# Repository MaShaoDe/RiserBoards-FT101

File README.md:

# RB Riser Boards for Yaesu FT-101 and Sommerkamp FT-277 Transceivers

*Because aligning a plug-in card with your nose inside the chassis is a tradition no OM or YL needs to keep.*

**No CAD skills needed, no special tools, no excuses.** Grab the Gerber ZIP, upload it to JLCPCB, order a card edge connector, and a week later the postman brings you a pack of shiny gold fingered boards. Heat up the iron, solder 36 joints, beep them through, and your FT-101 opens up like it never did before. That is the DIY spirit that built ham radio: you build it, you understand it, you fix it. Let's go!

The Yaesu FT-101 family, sold in Europe as the Sommerkamp FT-277, earned the nickname "the workhorse" for good reason: almost every circuit sits on a plug-in card that drops into an edge connector in the chassis. Great for service. Less great when you want to measure a card while it is running, because then it is buried between its neighbours.

A riser board solves that, QSL? It plugs into the socket in the radio, and the card plugs into the riser. The card now stands about 10 cm higher, in line with its original position, and every trimmer, test point and component is within reach of your probe. Each contact also gets its own test pad on the riser, top and bottom.

## Which radios?

Every model of the original series with plug-in cards:

| Brand | Models |
|---|---|
| Yaesu | FT-101 (Mk I, Mk II), FT-101B, FT-101E, FT-101EE, FT-101EX, FT-101F, FT-101FE, FT-101FX (plus the Japanese BS and ES versions) |
| Sommerkamp | FT-277, FT-277B, FT-277E, FT-277EE |

Not for the FT-101Z and FT-101ZD. Despite the name they are a different design without plug-in cards. Sorry, Z owners, negative copy on this one.

## Which riser for which card?

The number in the name is the count of contacts per side. That is also how to pick one: count the fingers on one side of your card, or measure the width of the finger zone.

| Riser | Contacts | Finger zone | Cards | Status |
|---|---|---|---|---|
| [RB10](hardware/riser-2x10) | 2x10 | 42 mm | PB-1292 noise blanker | V0.3 in production |
| [RB14](hardware/riser-2x14) | 2x14 | 57 mm | PB-1184A modulator and oscillator | V0.3 in production |
| [RB18](hardware/riser-2x18) | 2x18 | 73 mm | PB-1180B HF IF, PB-1181B RF, PB-1314 regulator | V0.1 prototype built, V0.3 in production |
| [RB22](hardware/riser-2x22) | 2x22 | 89 mm | PB-1183B IF, PB-1315A AF | V0.3 in production |

Card names vary between production runs. If your card has the right width, it fits.

## Build one in four steps

1. **Download** the Gerber ZIP of your riser: [RB10](hardware/riser-2x10/RB10_V0.3_gerber.zip), [RB14](hardware/riser-2x14/RB14_V0.3_gerber.zip), [RB18](hardware/riser-2x18/RB18_V0.3_gerber.zip) or [RB22](hardware/riser-2x22/RB22_V0.3_gerber.zip).
2. **Order** bare boards at the PCB maker of your choice. The fabrication specification is in [docs/ordering.md](docs/ordering.md). The one thing you must not forget: **gold fingers**, 1.6 mm, ENIG.
3. **Buy** one card edge connector per board, see [docs/bom.md](docs/bom.md).
4. **Solder** the connector and start measuring, see [docs/assembly.md](docs/assembly.md).

Total cost for five RB18 boards plus connectors: roughly the price of a nice dinner for two, and a lot less than a burnt card. Share the spare boards with the OMs in your club and the whole local net is QRV for service.

## What is on the board

- FR4, 1.6 mm, 105 mm long, in-line design: the card stands straight above the socket
- Hard gold edge fingers on both sides with a bevelled tip
- 2 mm traces, top and bottom kept separate, all covered by solder mask
- One test pad per contact on both sides, in line with the card's pins
- Clear silkscreen: riser type, compatible radios, "COMPONENT SIDE" and an arrow towards the radio, so the card goes in the right way round
- No pin numbers printed. The cards in this family number their pins in different directions, so the riser would be wrong on half of them. Read the number on the card itself.

## A word about RF and IF cards

The riser makes the signal path about 10 cm longer. Supply voltages, bias and audio do not care. Tuned RF and IF circuits (PB-1180B, PB-1181B, PB-1183B) may, and you would rather not hunt self-made QRM. Use the riser there to measure voltages and levels, and do the fine alignment with the card back in its own socket.

## Contents

- [docs/specification.md](docs/specification.md): measurements, design decisions, open questions
- [docs/ordering.md](docs/ordering.md): fabrication specification for any PCB maker
- [docs/bom.md](docs/bom.md): parts to buy
- [docs/assembly.md](docs/assembly.md): soldering, checking and using the riser
- `hardware/`: one folder per riser with the Gerber ZIP and a picture of both sides
- `hardware/archive/`: Gerber files of the first RB18 prototype (V0.1)

## Licenses

- Hardware (Gerber files): CERN-OHL-P-2.0
- Documentation and pictures: CC-BY-4.0

See [LICENSE.md](LICENSE.md). You may build, sell and modify the boards. If you change the design, please give it a name of your own and do not call it RB10, RB14, RB18 or RB22, so that the tested original stays recognisable.

## Disclaimer

Use at your own risk. The FT-101 carries high voltages in the PA section, and the riser does not change that. This project has no connection to Yaesu or Sommerkamp. The names are used only to state compatibility.

## Contributing

Measurements of other cards, corrections, photos and stories of successful repairs are welcome. Open an issue or a pull request, we copy you 5 and 9.

Questions, ideas or wishes for changes? Just call in by opening an issue on GitHub. No promises on what gets built or when, this is a hobby project run in spare time between QSOs, but every message is read and the band is always open.

## Thank you

To Yaesu for building a radio that people still repair with love fifty years later, to Sommerkamp for bringing it to Europe, to everyone who keeps the service manuals and board lists online, and to every OM and YL who keeps an old workhorse on the air.

May your filaments glow and your SWR stay flat.

73 de Marcel (MaShaoDe)

Copyright 2026 FerienBSD aka Marcel Sauder (MaShaoDe)

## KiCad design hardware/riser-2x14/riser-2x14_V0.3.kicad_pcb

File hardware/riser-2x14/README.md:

# RB14: Riser 2x14 (28 contacts)

For cards: PB-1184 (modulator and oscillator)

Current version: **V0.3**, in production since 2026-11-25.

## Files

| File | Content |
|---|---|
| [`RB14_V0.3_gerber.zip`](RB14_V0.3_gerber.zip) | Gerber and drill files, ready to upload to any PCB maker |
| `RB14_V0.3.png` | Both sides, rendered from the Gerber files |

## Board

| Item | Value |
|---|---|
| Outline | 62 x 105 mm (finger zone 57 mm wide, 11 mm long) |
| Contacts | 2x14, pitch 3.96 mm, contact field 51.48 mm |
| Edge fingers | 2.0 x 9.0 mm, both sides |
| Test pads | round 2.6 mm, both sides, one per contact |
| Connector pads | 2.0 x 5.0 mm, both sides |

Fabrication settings: [../../docs/ordering.md](../../docs/ordering.md). Connector: [../../docs/bom.md](../../docs/bom.md). Soldering and use: [../../docs/assembly.md](../../docs/assembly.md).

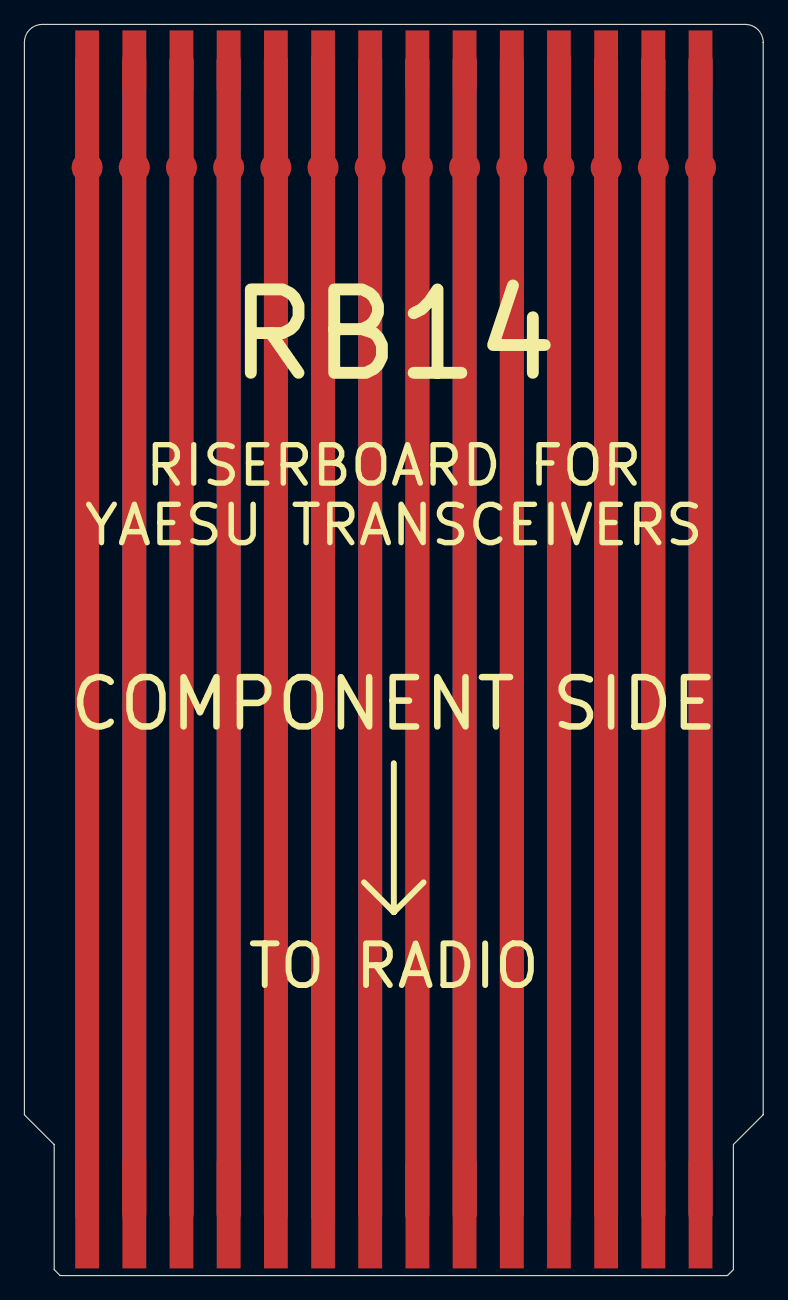
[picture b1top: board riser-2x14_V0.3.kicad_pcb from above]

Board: 2 copper layers, 62.0 x 105.0 mm, 3 parts (0 on the bottom side), 28 nets.

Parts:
J1: EdgeFingers_2x14
J2: ConnectorPads_2x14
TP1: TestPads_2x14

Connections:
POS01B: J1.1B, J2.1B, TP1.1B
POS01F: J1.1, J2.1, TP1.1
POS02B: J1.2B, J2.2B, TP1.2B
POS02F: J1.2, J2.2, TP1.2
POS03B: J1.3B, J2.3B, TP1.3B
POS03F: J1.3, J2.3, TP1.3
POS04B: J1.4B, J2.4B, TP1.4B
POS04F: J1.4, J2.4, TP1.4
POS05B: J1.5B, J2.5B, TP1.5B
POS05F: J1.5, J2.5, TP1.5
POS06B: J1.6B, J2.6B, TP1.6B
POS06F: J1.6, J2.6, TP1.6
POS07B: J1.7B, J2.7B, TP1.7B
POS07F: J1.7, J2.7, TP1.7
POS08B: J1.8B, J2.8B, TP1.8B
POS08F: J1.8, J2.8, TP1.8
POS09B: J1.9B, J2.9B, TP1.9B
POS09F: J1.9, J2.9, TP1.9
POS10B: J1.10B, J2.10B, TP1.10B
POS10F: J1.10, J2.10, TP1.10
POS11B: J1.11B, J2.11B, TP1.11B
POS11F: J1.11, J2.11, TP1.11
POS12B: J1.12B, J2.12B, TP1.12B
POS12F: J1.12, J2.12, TP1.12
POS13B: J1.13B, J2.13B, TP1.13B
POS13F: J1.13, J2.13, TP1.13
POS14B: J1.14B, J2.14B, TP1.14B
POS14F: J1.14, J2.14, TP1.14

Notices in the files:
hardware/riser-2x14/riser-2x14_V0.3.kicad_pcb:
V0.3  CERN-OHL-P-2.0
